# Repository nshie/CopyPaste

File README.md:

# CopyPaste
Split 40% Bluetooth Keyboard

### Motivation
I wanted a portable, light keyboard to bring to class, with stenography (chording) and bluetooth capabilities.

### Design
- symmetrical design so both sides of the PCB can be soldered to get the left and right halves
  - JLCPCB minimum order quantity is 5, so might as well use 2/5 instead of buying 2 different PCBs and using 2/10
- choc low profile switches for portability
- nice!nano for easy hand soldering (as opposed to soldering my own MCUs)
- thumb switches as close together as possible for chording
- rotary encoder for alt-tab on the left, volume on the right
- ports for oled display (not recommended because of battery drain)
  - mounting holes for acrylic screen protector
- pads for ws2812b leds (not recommended because of battery drain)

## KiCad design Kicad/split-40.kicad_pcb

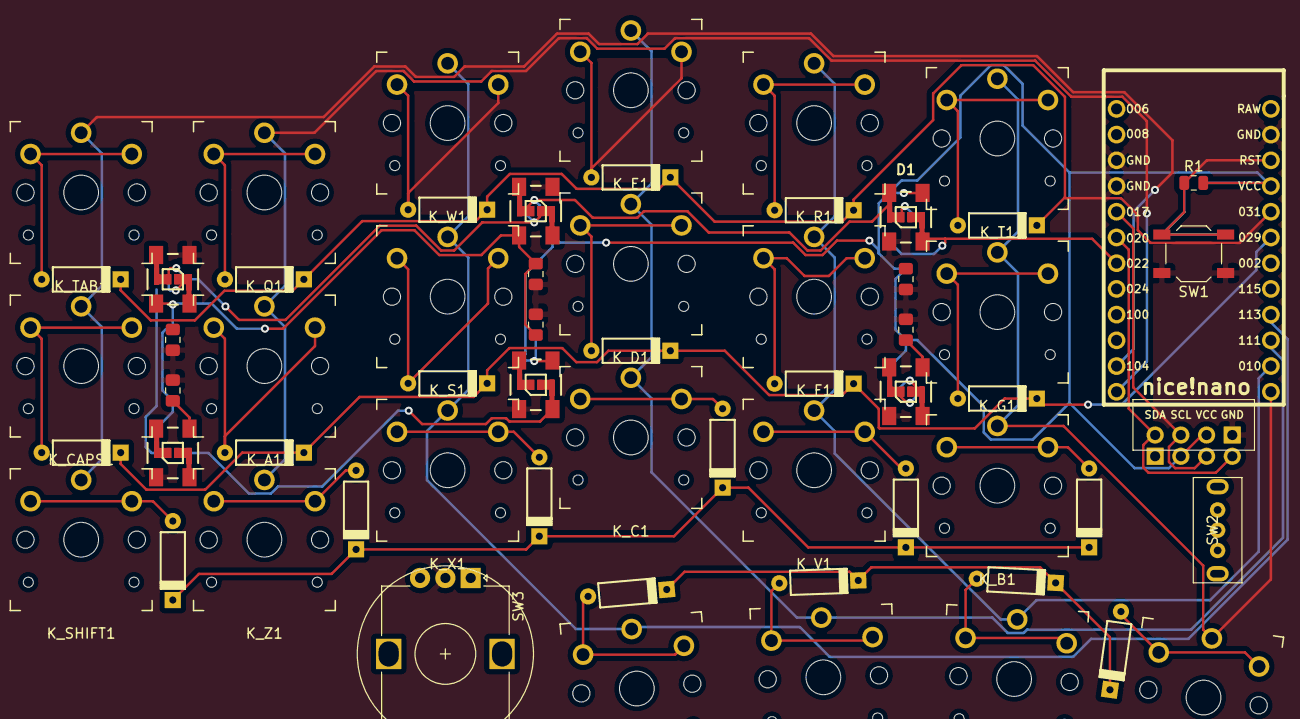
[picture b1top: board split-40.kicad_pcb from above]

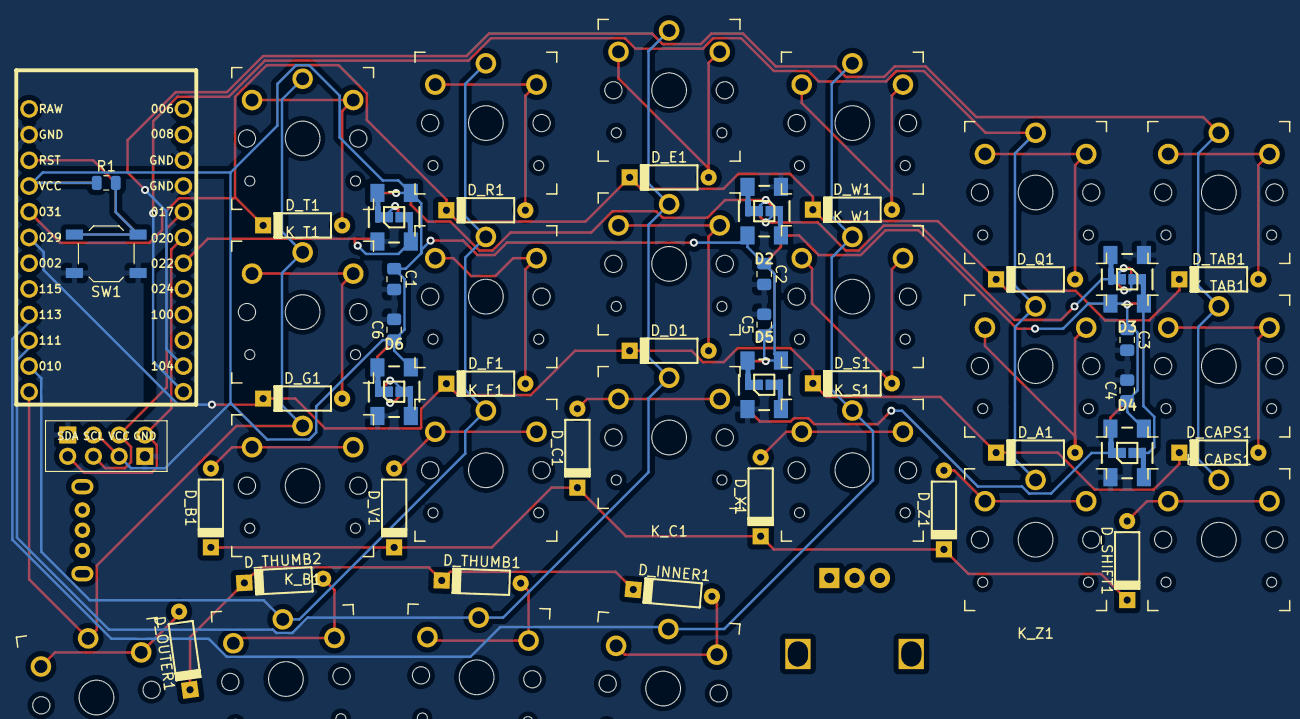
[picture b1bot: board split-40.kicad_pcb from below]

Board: 2 copper layers, 63 parts (36 on the bottom side), 46 nets.

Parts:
C1, C2, C3, C4, C5, C6: 0.1uF; C_0805_Reversible
D1, D2, D3, D4, D5, D6: WS2812B; WS2812B_data-bridgeable_Reversible
D_A1: D; D_axial_reversible
D_B1: D; D_axial_reversible
D_C1: D; D_axial_reversible
D_CAPS1: D; D_axial_reversible
D_D1: D; D_axial_reversible
D_E1: D; D_axial_reversible
D_F1: D; D_axial_reversible
D_G1: D; D_axial_reversible
D_INNER1: D; D_axial_reversible
D_OUTER1: D; D_axial_reversible
D_Q1: D; D_axial_reversible
D_R1: D; D_axial_reversible
D_S1: D; D_axial_reversible
D_SHIFT1: D; D_axial_reversible
D_T1: D; D_axial_reversible
D_TAB1: D; D_axial_reversible
D_THUMB1, D_THUMB2: D; D_axial_reversible
D_V1: D; D_axial_reversible
D_W1: D; D_axial_reversible
D_X1: D; D_axial_reversible
D_Z1: D; D_axial_reversible
K_A1: KEYSW; SW_PG1350_reversible_outlined
K_B1: KEYSW; SW_PG1350_reversible_outlined
K_C1: KEYSW; SW_PG1350_reversible_outlined
K_CAPS1: KEYSW; SW_PG1350_reversible_outlined
K_D1: KEYSW; SW_PG1350_reversible_outlined
K_E1: KEYSW; SW_PG1350_reversible_outlined
K_F1: KEYSW; SW_PG1350_reversible_outlined
K_G1: KEYSW; SW_PG1350_reversible_outlined
K_INNER1: KEYSW; SW_PG1350_reversible_outlined
K_OUTER1: KEYSW; SW_PG1350_reversible_outlined
K_Q1: KEYSW; SW_PG1350_reversible_outlined
K_R1: KEYSW; SW_PG1350_reversible_outlined
K_S1: KEYSW; SW_PG1350_reversible_outlined
K_SHIFT1: KEYSW; SW_PG1350_reversible_outlined
K_T1: KEYSW; SW_PG1350_reversible_outlined
K_TAB1: KEYSW; SW_PG1350_reversible_outlined
K_THUMB1, K_THUMB2: KEYSW; SW_PG1350_reversible_outlined
K_V1: KEYSW; SW_PG1350_reversible_outlined
K_W1: KEYSW; SW_PG1350_reversible_outlined
K_X1: KEYSW; SW_PG1350_reversible_outlined
K_Z1: KEYSW; SW_PG1350_reversible_outlined
L1, L1#2: SSD1306_OLED_Display; SSD1306-0.91-OLED-4pin-128x32
R1: 10k; R_0805_2012Metric
SW1: SW_Push; SW_SPST_TL3342
SW2: SW_SPDT; SK12D07VG3-Mini-SPDT-Slide-Switch-Right-Angle
SW3: Rotary_Encoder; RotaryEncoder_Alps_EC12E_Vertical_H20mm
U1: nice_nano

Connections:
GND: C1.2, C2.2, C3.2, C4.2, C5.2, C6.2, D1.3, D2.3, D3.3, D4.3, D5.3, D6.3, L1.1, L1#2.1, SW1.1, SW3.C, U1.3, U1.4, U1.23
unnamed: D1.2, D2.4
unnamed: D2.2, D3.4
unnamed: D3.2, D4.4
unnamed: D4.2, D5.4
unnamed: D5.2, D6.4
unnamed: D_A1.2, K_A1.2
unnamed: D_B1.2, K_B1.2
unnamed: D_C1.2, K_C1.2
unnamed: D_CAPS1.2, K_CAPS1.2
unnamed: D_D1.2, K_D1.2
unnamed: D_E1.2, K_E1.2
unnamed: D_F1.2, K_F1.2
unnamed: D_G1.2, K_G1.2
unnamed: D_INNER1.2, K_INNER1.2
unnamed: D_OUTER1.2, K_OUTER1.2
unnamed: D_Q1.2, K_Q1.2
unnamed: D_R1.2, K_R1.2
unnamed: D_S1.2, K_S1.2
unnamed: D_SHIFT1.2, K_SHIFT1.2
unnamed: D_T1.2, K_T1.2
unnamed: D_TAB1.2, K_TAB1.2
unnamed: D_THUMB1.2, K_THUMB1.2
unnamed: D_THUMB2.2, K_THUMB2.2
unnamed: D_V1.2, K_V1.2
unnamed: D_W1.2, K_W1.2
unnamed: D_X1.2, K_X1.2
unnamed: D_Z1.2, K_Z1.2
unnamed: R1.2, SW1.2, U1.22
unnamed: SW2.1, U1.24
SCL: L1.3, L1#2.3, U1.5
SDA: L1.4, L1#2.4, U1.6
VCC: C1.1, C2.1, C3.1, C4.1, C5.1, C6.1, D1.1, D2.1, D3.1, D4.1, D5.1, D6.1, L1.2, L1#2.2, R1.1, U1.21
col0: K_CAPS1.1, K_SHIFT1.1, K_TAB1.1, U1.11
col1: K_A1.1, K_Q1.1, K_Z1.1, U1.12
col2: K_INNER1.1, K_S1.1, K_W1.1, K_X1.1, U1.16
col3: K_C1.1, K_D1.1, K_E1.1, K_THUMB1.1, U1.15
col4: K_F1.1, K_R1.1, K_THUMB2.1, K_V1.1, U1.14
col5: K_B1.1, K_G1.1, K_OUTER1.1, K_T1.1, U1.13
encA: SW3.A, U1.1
encB: SW3.B, U1.2
led: D1.4, U1.7
row0: D_E1.1, D_Q1.1, D_R1.1, D_T1.1, D_TAB1.1, D_W1.1, U1.20
row1: D_A1.1, D_CAPS1.1, D_D1.1, D_F1.1, D_G1.1, D_S1.1, U1.19
row2: D_B1.1, D_C1.1, D_SHIFT1.1, D_V1.1, D_X1.1, D_Z1.1, U1.18
row3: D_INNER1.1, D_OUTER1.1, D_THUMB1.1, D_THUMB2.1, U1.17

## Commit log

2023-10-15 Added images
2023-10-15 Resized images
